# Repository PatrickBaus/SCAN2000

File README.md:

# Keithley 2000-SCAN SSR Replacement

This repository contains the KiCAD PCB project files for a [Keithley Model 2000-SCAN](https://download.tek.com/manual/2000SCAN-901-01_F-Jan-2014.pdf) replacement card. It uses solid-state relays instead of mechanical relays. See [below](#introduction) for a list of compatible devices. The design files can be found on the [releases](../../releases) page.

## Contents
- [Introduction](#introduction)
- [Design Files](#design-files)
- [Installation](#installation)
- [Accesories](#accesories)
- [Related Repositories](#related-repositories)
- [Versioning](#versioning)
- [License](#license)

## Introduction
The design is the successor of the SCAN2000 STM32 board previously released as [v1.x](https://github.com/PatrickBaus/SCAN2000/tree/v1). Instead of an STM32 microcontroller it uses an [iCE40](https://www.latticesemi.com/iCE40) FPGA to emulate the shift registers found on the 10 channel [Model 2000-SCAN](https://download.tek.com/manual/2000SCAN-901-01_F-Jan-2014.pdf) card and is also capable of decoding the protcol used by the 20-channel [Model 2000-SCAN-20](https://download.tek.com/manual/2000-20-901-01C_Jul2003_Instruction.pdf). The advantage of the FPGA is that the shift registers are implemented in hardware. The protocol spoken by the 10 channnel card requires freezing 24 bits clocked in _before_ the strobe bin is triggered, similar to the positive lookahead assertion of a [regular expression](https://en.wikipedia.org/wiki/Regular_expression). This is in stark contrast to typical protocols used by microcontrollers like, for example, [SPI](https://en.wikipedia.org/wiki/Serial_Peripheral_Interface) that uses a [chip select](https://en.wikipedia.org/wiki/Chip_select) control line to announce incoming data arriving _after_ the CS signal. A more detailed analysis of the problem can be found in the [doc/](doc/) folder.

The card was tested in a [Keithley DMM6500](https://www.tek.com/en/products/keithley/digital-multimeter/dmm6500) and a [Keithley Model 2002](https://www.tek.com/en/products/keithley/digital-multimeter/2002-series) in both configurations as a 10 channel and 20 channel card. The more recent [Keithley DMM6500](https://www.tek.com/en/products/keithley/digital-multimeter/dmm6500) supports both the older 10 channel [Model 2000-SCAN](https://download.tek.com/manual/2000SCAN-901-01_F-Jan-2014.pdf) and the newer [Model 2000-SCAN-20](https://download.tek.com/manual/2000-20-901-01C_Jul2003_Instruction.pdf) 20 channel scanner card. The same goes for the [Model 2000](https://www.tek.com/en/products/keithley/digital-multimeter/keithley-2000-series-6-digit-multimeter-scanning) and Model 2000-20. The Model 2000-20 is similar to the [Model 2000](https://www.tek.com/en/products/keithley/digital-multimeter/keithley-2000-series-6-digit-multimeter-scanning), but has a different firmware. The latest firmare of the [Model 2000](https://www.tek.com/en/products/keithley/digital-multimeter/keithley-2000-series-6-digit-multimeter-scanning) seems to support the 20 channel cards as well as suggested [here](https://www.eevblog.com/forum/circuit-studio/example-project-20-channel-solid-state-scan-card-for-k2000-dmm/msg3101128/#msg3101128). The [Model 2002](https://www.tek.com/en/products/keithley/digital-multimeter/2002-series) only supports 10 channel cards.

|DMM|Tested|Note|
|--|--|--|
|[DMM6500](https://www.tek.com/en/products/keithley/digital-multimeter/dmm6500)|:heavy_check_mark:|Works.|
|[2000](https://www.tek.com/en/products/keithley/digital-multimeter/keithley-2000-series-6-digit-multimeter-scanning)|:x:|Not tested, but should work. The latest firmware seems to support [20 channels](https://www.eevblog.com/forum/circuit-studio/example-project-20-channel-solid-state-scan-card-for-k2000-dmm/msg3101128/#msg3101128).|
|[2000-20](https://www.tek.com/en/products/keithley/digital-multimeter/keithley-2000-series-6-digit-multimeter-scanning)|:x:|Not tested, but should work.|
|[2010](https://www.tek.com/en/products/keithley/digital-multimeter/2010-series)|:heavy_check_mark:|Works, but only 10 channels cards are supported by the firmware.|
|[2001](https://www.tek.com/en/products/keithley/digital-multimeter/2001-series)|:x:|Not tested, but should work.|
|[2002](https://www.tek.com/en/products/keithley/digital-multimeter/2002-series)|:heavy_check_mark:|Works. Only 10 channels supported.|

## Design Files
The root folder contains the KiCAD files. The bill of materials can be found on the [releases](../../releases) page along with Gerber files for production.

## Installation
The source code for the FPGA and the installation instructions for the firmware can be found [here](https://github.com/PatrickBaus/SCAN2000_iCE40_Firmware). The FPGA source code must be written to the onboard SPI flash chip. One way to do so is to use an USB to SPI converter with an FT232H chip.

The SCAN2000 SSR board has two solder jumpers, ```JP1``` and ```JP2```. To enable only 10 channels close ```JP2``` and connect the two left pads of ```JP1``` together using a soldering iron. To enable 20 channel operation, leave ```JP2``` open and connect the two rightmost pads of ```JP1```.

The assembled card can then wired up and simply inserted into the multimeter. It will be supplied by the DMM through the Molex connector. To connect the scanner outputs to the, connect the screw terminals labeled ```Input``` to the DMM terminals labeled ```Input```. The same goes for the ```Sense``` terminals if operating in 4-wire mode.

## Accesories
The [Model 2000-SCAN](https://download.tek.com/manual/2000SCAN-901-01_F-Jan-2014.pdf) comes with four 10″ connectors that have a right angle 4 mm connector on one side and a tinned wire on the other. They are sold by Keithley as [CA-109A](https://download.tek.com/document/1KW-50660-1_Keithley_Test_Leads_Probes_Selector_Guide_100622.pdf) and are made by Mueller Electric. Their part numbers are [BU-0062-N-108-2 (red)](https://www.muellerelectric.com/products/bu-0062-n-108-2) and [BU-0062-N-108-0 (black)](https://www.muellerelectric.com/products/bu-0062-n-108-0). Keithley shortens the Mueller Electric parts to 10″. The same length is fine for this board as well.

## Related Repositories
See the following repositories for more information as these are part of the [design files](#design-files).

- [KiCad footprints](https://github.com/PatrickBaus/footprints.pretty)
- [KiCAD 3D models](https://github.com/PatrickBaus/footprints.3dshapes)
- [KiCAD schematic libraries](https://github.com/PatrickBaus/KiCad-libraries)

## Versioning
I use [SemVer](http://semver.org/) for versioning. For the versions available, see the [tags](../../tags) available for this repository.

- MAJOR versions in this context mean a breaking change to the external interface of the hardware like different connectors or functions.
- MINOR versions contain changes to the hardware that only affect the inner workings of the circuit, but otherwise the performance is unaffected.
- PATCH versions do not affect the schematics or invalidate older bill of materials. These changes may include updated components (to replace obsolete parts for example), an updated silkscreen, or fixed typos.

## License
This work is released under the CERN-OHL-W
See [https://ohwr.org/cern_ohl_w_v2.pdf](https://ohwr.org/cern_ohl_w_v2.pdf) or the included LICENSE file for more information.

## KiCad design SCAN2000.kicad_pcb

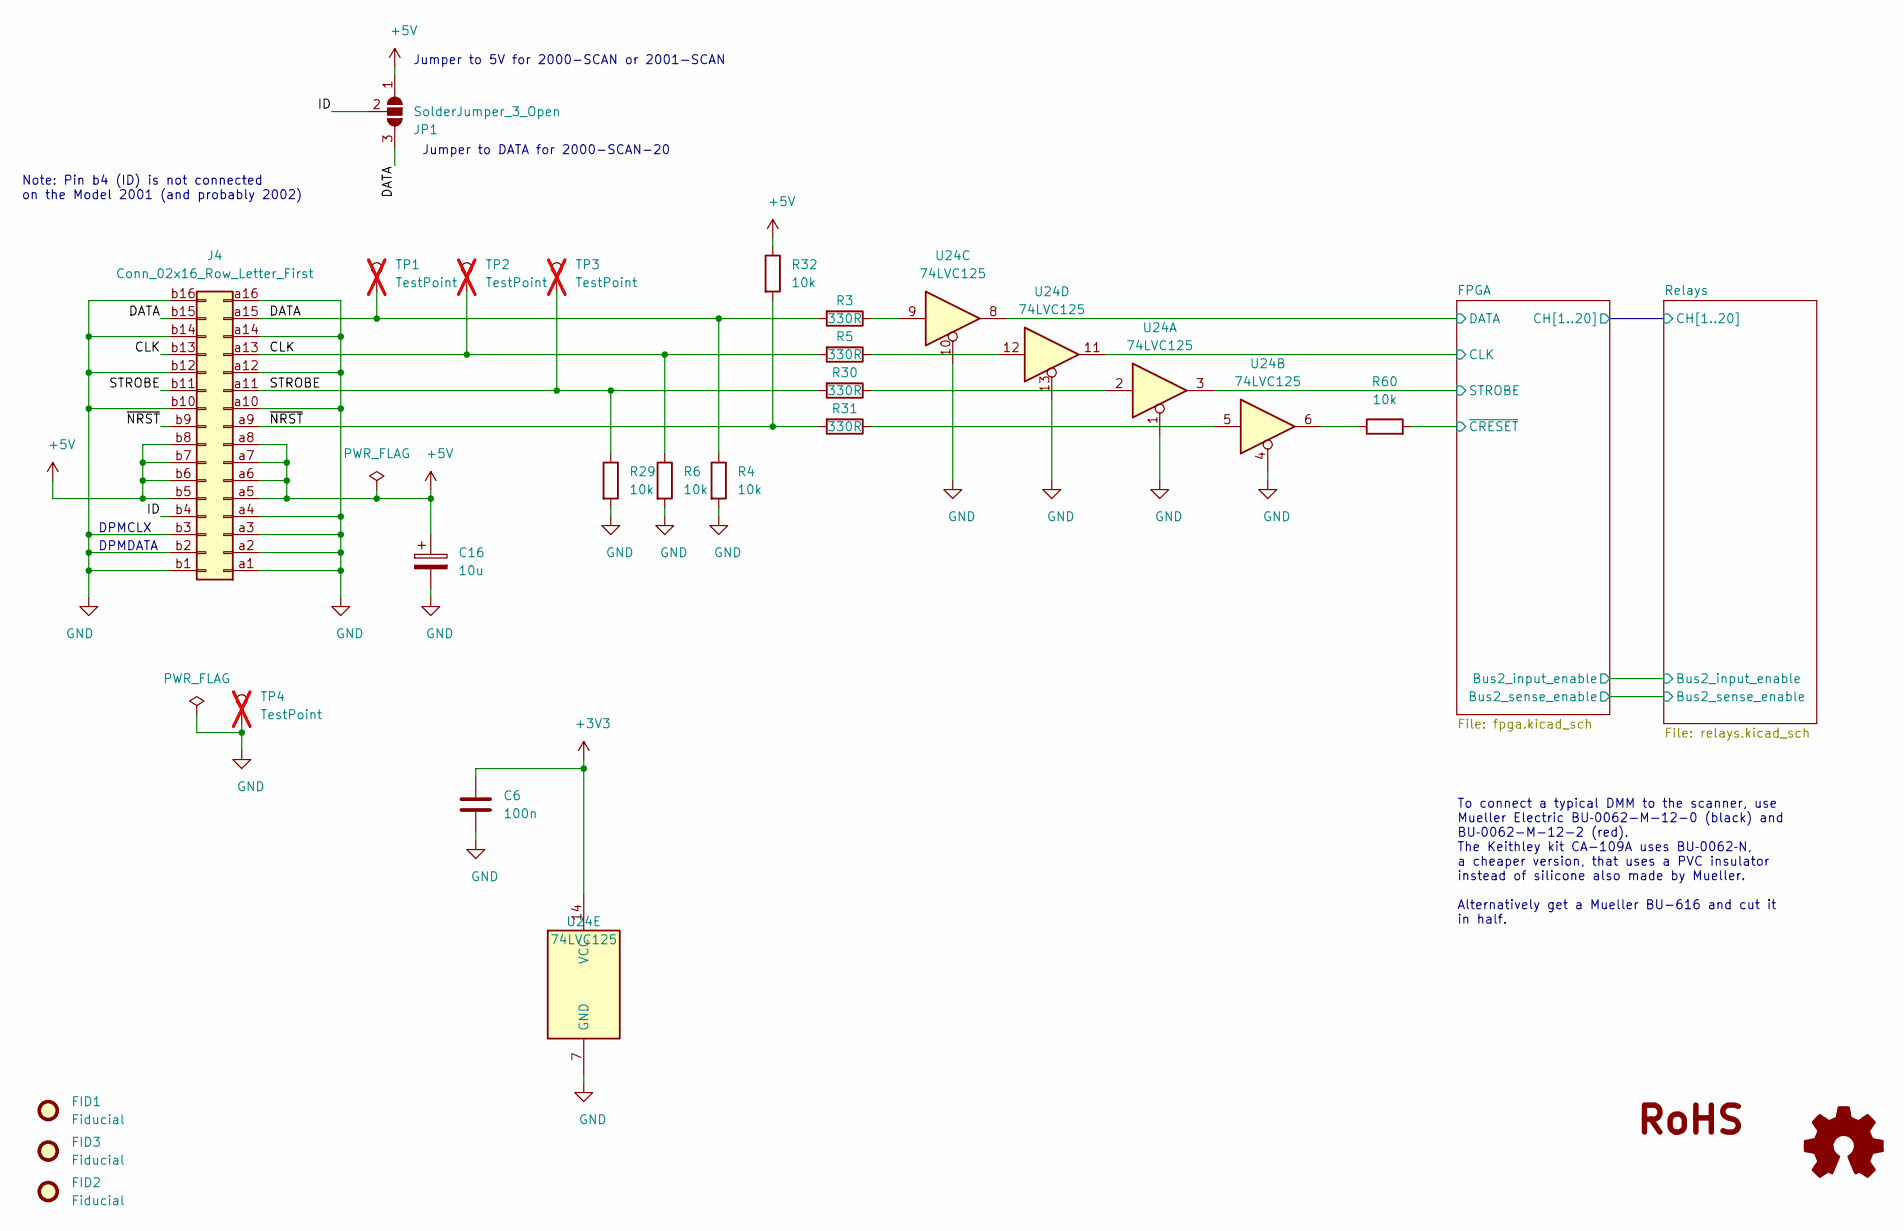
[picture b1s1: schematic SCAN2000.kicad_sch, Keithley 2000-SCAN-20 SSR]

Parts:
C6: 100n; C_0603_1608Metric
C16: 10u; CP_Radial_D6.3mm_P2.50mm
FID1, FID2, FID3: Fiducial; Fiducial_0.5mm_Mask1mm
J4: Conn_02x16_Row_Letter_First; DIN41612_B2_2x16_Male_Horizontal_THT; Digikey# 09272326804-ND
JP1: SolderJumper_3_Open; SolderJumper-3_P1.3mm_Open_Pad1.0x1.5mm
LOGO1: Logo_Open_Hardware_Small; OSHW-Logo_7.5x8mm_SilkScreen
R3, R5, R30, R31: 330R; R_0603_1608Metric
R4, R6, R29, R32, R60: 10k; R_0603_1608Metric
TP1, TP2, TP3, TP4: TestPoint; TestPoint_Loop_D2.60mm_Drill1.6mm_Beaded; not fitted
U24: 74LVC125; TSSOP-14_4.4x5mm_P0.65mm

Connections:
+3V3: C6.1, U24.14 (VCC); also elsewhere on the board
+5V: C16.1, J4.a5, J4.a6, J4.a7, J4.a8, J4.b5, J4.b6, J4.b7, J4.b8, JP1.1 (A), R32.1; also elsewhere on the board
/CLK: J4.a13, J4.b13, R5.2, R6.1, TP2.1
/DATA: J4.a15, J4.b15, JP1.3 (B), R3.2, R4.1, TP1.1
/FPGA/CLK: U24.11; also elsewhere on the board
/FPGA/DATA: U24.8; also elsewhere on the board
/FPGA/STROBE: U24.3; also elsewhere on the board
/FPGA/~CRESET: R60.2; also elsewhere on the board
/ID: J4.b4, JP1.2 (C)
/STROBE: J4.a11, J4.b11, R29.1, R30.2, TP3.1
/~NRST: J4.a9, J4.b9, R31.2, R32.2
GND: C6.2, C16.2, J4.a1, J4.a2, J4.a3, J4.a4, J4.a10, J4.a12, J4.a14, J4.a16, J4.b1, J4.b2, J4.b3, J4.b10, J4.b12, J4.b14, J4.b16, R4.2, R6.2, R29.2, TP4.1, U24.1, U24.4, U24.7 (GND), U24.10, U24.13; also elsewhere on the board
unnamed: R3.1, U24.9
unnamed: R5.1, U24.12
unnamed: R30.1, U24.2
unnamed: R31.1, U24.5
unnamed: R60.1, U24.6

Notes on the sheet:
DPMDATA
DPMCLX
Jumper to 5V for 2000-SCAN or 2001-SCAN
Jumper to DATA for 2000-SCAN-20
To connect a typical DMM to the scanner, use Mueller Electric BU‐0062-M-12-0 (black) and BU‐0062-M-12-2 (red). The Keithley kit CA-109A uses BU‐0062‐N, a cheaper version, that uses a PVC insulator instead of silicone also made by Mueller. Alternatively get a Mueller BU-616 and cut it in half.
Note: Pin b4 (ID) is not connected on the Model 2001 (and probably 2002)

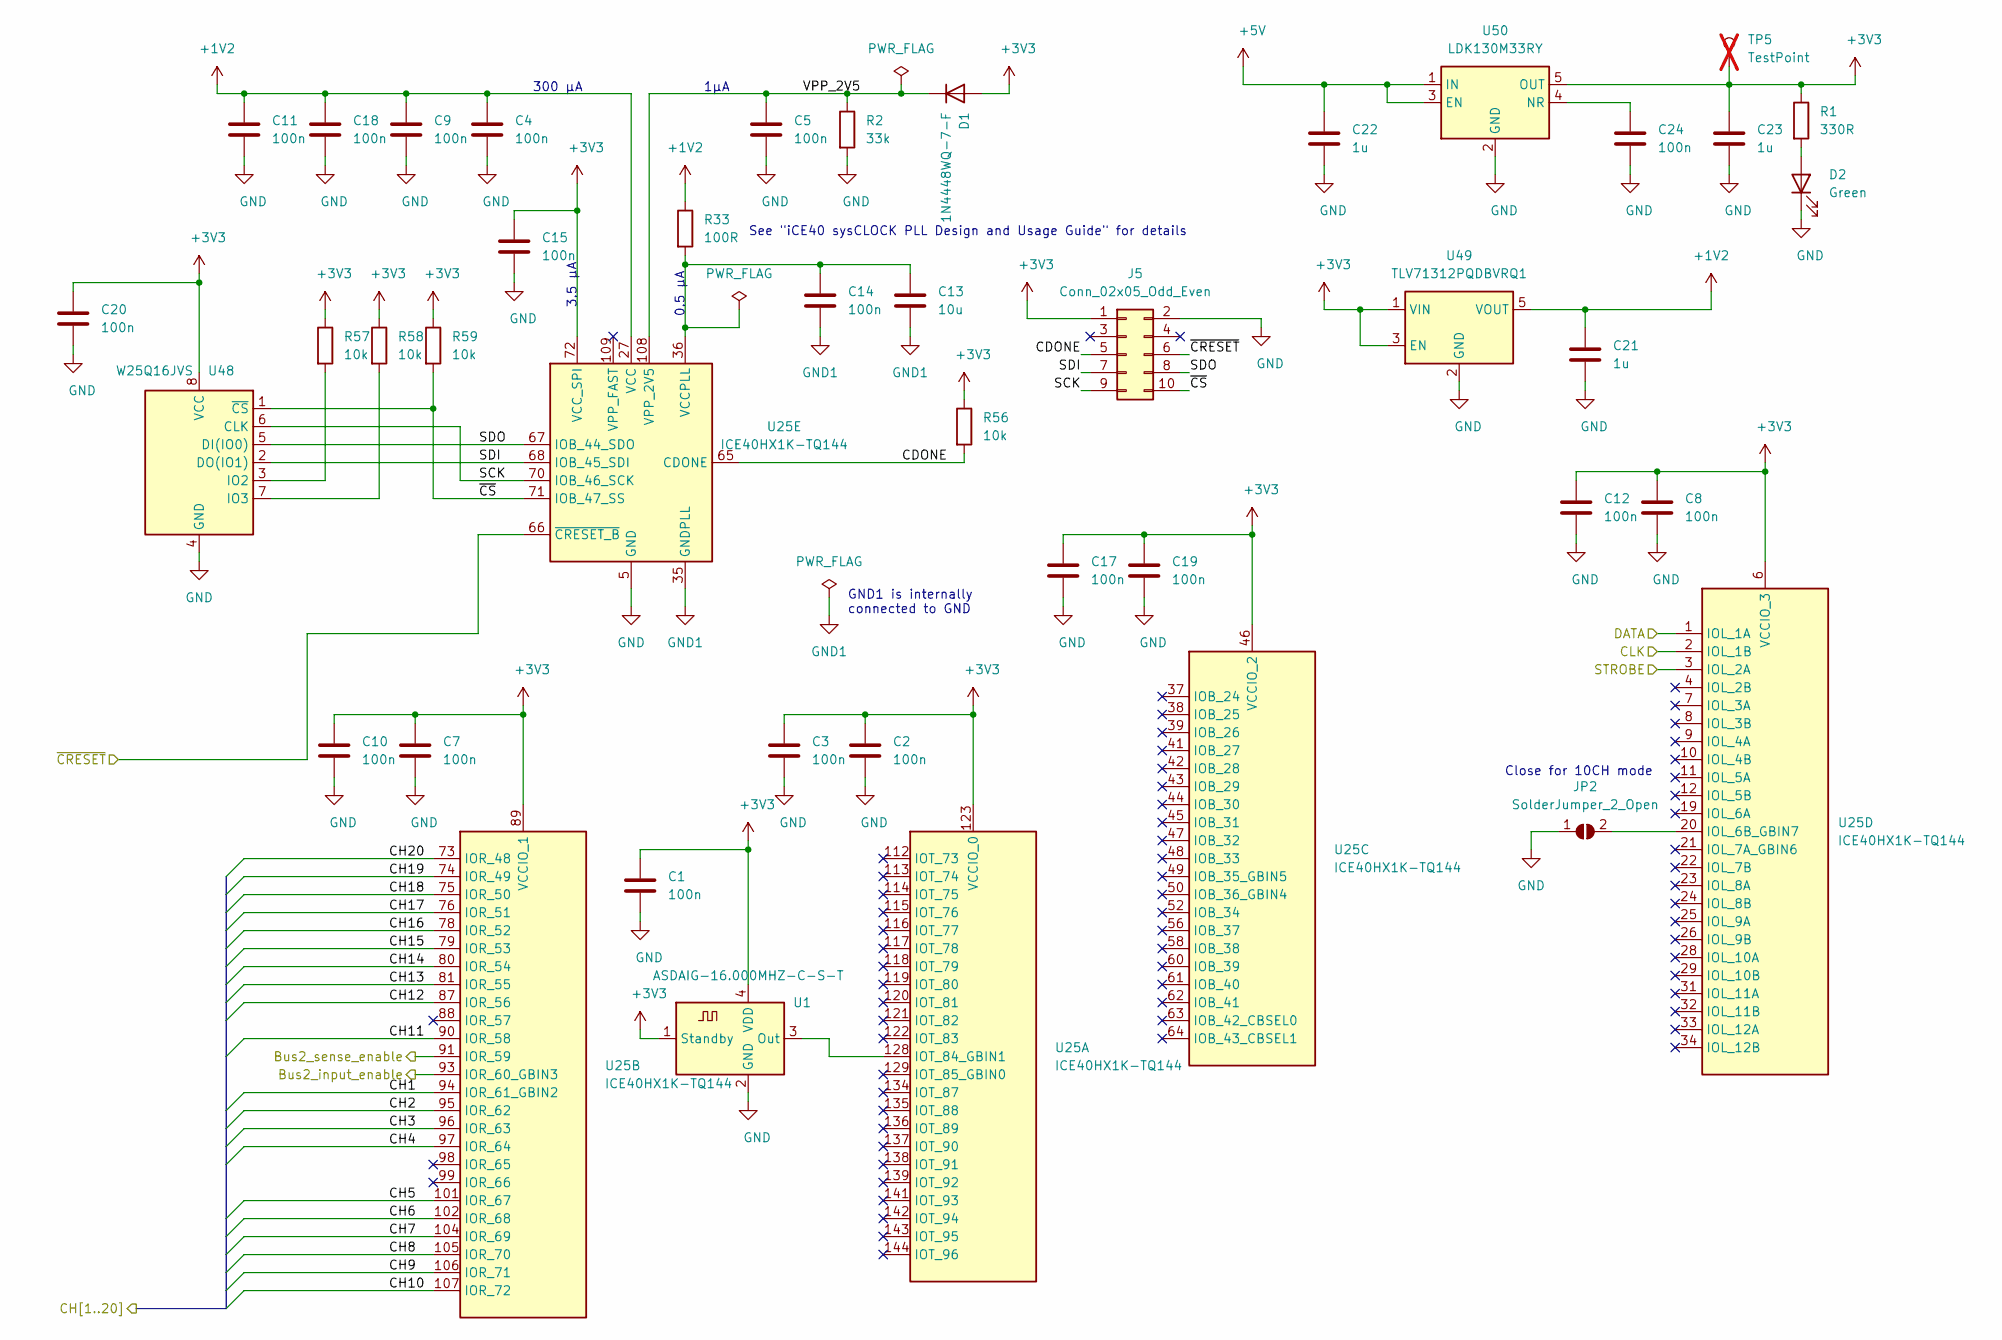
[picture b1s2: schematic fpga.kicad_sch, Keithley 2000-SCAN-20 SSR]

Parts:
C1, C2, C3, C4, C5, C7, C8, C9, C10, C11, C12, C14, C15, C17, C18, C19, C20, C24: 100n; C_0603_1608Metric
C13: 10u; C_0805_2012Metric
C21, C22, C23: 1u; C_0805_2012Metric
D1: 1N4448WQ-7-F; D_SOD-123
D2: Green; LED_0603_1608Metric
J5: Conn_02x05_Odd_Even; IDC-Header_2x05_P2.54mm_Vertical
JP2: SolderJumper_2_Open; SolderJumper-2_P1.3mm_Open_Pad1.0x1.5mm
R1: 330R; R_0603_1608Metric
R2: 33k; R_0603_1608Metric
R33: 100R; R_0603_1608Metric
R56, R57, R58, R59: 10k; R_0603_1608Metric
TP5: TestPoint; TestPoint_Loop_D2.60mm_Drill1.6mm_Beaded; not fitted
U1: ASDAIG-16.000MHZ-C-S-T; Oscillator_SMD_Abracon_ASDMB-4Pin_2.5x2.0mm
U25: ICE40HX1K-TQ144; TQFP-144_20x20mm_P0.5mm
U48: W25Q16JVS; SOIC-8_3.9x4.9mm_P1.27mm
U49: TLV71312PQDBVRQ1; SOT-23-5
U50: LDK130M33RY; SOT-23-5

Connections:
+1V2: C4.1, C9.1, C11.1, C18.1, C21.1, R33.1, U25.27 (VCC), U25.51 (VCC), U25.92 (VCC), U25.111 (VCC), U49.5 (VOUT)
+3V3: C1.1, C2.1, C3.1, C7.1, C8.1, C10.1, C12.1, C15.1, C17.1, C19.1, C20.1, C23.1, D1.2 (A), J5.1, R1.1, R56.1, R57.1, R58.1, R59.1, TP5.1, U1.1 (Standby), U1.4 (VDD), U25.6 (VCCIO_3), U25.30 (VCCIO_3), U25.46 (VCCIO_2), U25.57 (VCCIO_2), U25.72 (VCC_SPI), U25.89 (VCCIO_1), U25.100 (VCCIO_1), U25.123 (VCCIO_0), U25.133 (VCCIO_0), U48.8 (VCC), U49.1 (VIN), U49.3 (EN), U50.5 (OUT); also elsewhere on the board
+5V: C22.1, U50.1 (IN), U50.3 (EN); also elsewhere on the board
/FPGA/Bus2_input_enable: U25.93 (IOR_60_GBIN3); also elsewhere on the board
/FPGA/Bus2_sense_enable: U25.91 (IOR_59); also elsewhere on the board
/FPGA/CDONE: J5.5, R56.2, U25.65 (CDONE)
/FPGA/CH1: U25.94 (IOR_61_GBIN2); also elsewhere on the board
/FPGA/CH2: U25.95 (IOR_62); also elsewhere on the board
/FPGA/CH3: U25.96 (IOR_63); also elsewhere on the board
/FPGA/CH4: U25.97 (IOR_64); also elsewhere on the board
/FPGA/CH5: U25.101 (IOR_67); also elsewhere on the board
/FPGA/CH6: U25.102 (IOR_68); also elsewhere on the board
/FPGA/CH7: U25.104 (IOR_69); also elsewhere on the board
/FPGA/CH8: U25.105 (IOR_70); also elsewhere on the board
/FPGA/CH9: U25.106 (IOR_71); also elsewhere on the board
/FPGA/CH10: U25.107 (IOR_72); also elsewhere on the board
/FPGA/CH11: U25.90 (IOR_58); also elsewhere on the board
/FPGA/CH12: U25.87 (IOR_56); also elsewhere on the board
/FPGA/CH13: U25.81 (IOR_55); also elsewhere on the board
/FPGA/CH14: U25.80 (IOR_54); also elsewhere on the board
/FPGA/CH15: U25.79 (IOR_53); also elsewhere on the board
/FPGA/CH16: U25.78 (IOR_52); also elsewhere on the board
/FPGA/CH17: U25.76 (IOR_51); also elsewhere on the board
/FPGA/CH18: U25.75 (IOR_50); also elsewhere on the board
/FPGA/CH19: U25.74 (IOR_49); also elsewhere on the board
/FPGA/CH20: U25.73 (IOR_48); also elsewhere on the board
/FPGA/CLK: U25.2 (IOL_1B); also elsewhere on the board
/FPGA/DATA: U25.1 (IOL_1A); also elsewhere on the board
/FPGA/SCK: J5.9, U25.70 (IOB_46_SCK), U48.6 (CLK)
/FPGA/SDI: J5.7, U25.68 (IOB_45_SDI), U48.2 (DO(IO1))
/FPGA/SDO: J5.8, U25.67 (IOB_44_SDO), U48.5 (DI(IO0))
/FPGA/STROBE: U25.3 (IOL_2A); also elsewhere on the board
/FPGA/VPP_2V5: C5.1, D1.1 (K), R2.1, U25.108 (VPP_2V5)
/FPGA/~CRESET: J5.6, U25.66 (~CRESET_B); also elsewhere on the board
/FPGA/~CS: J5.10, R59.2, U25.71 (IOB_47_SS), U48.1 (~CS)
GND: C1.2, C2.2, C3.2, C4.2, C5.2, C7.2, C8.2, C9.2, C10.2, C11.2, C12.2, C15.2, C17.2, C18.2, C19.2, C20.2, C21.2, C22.2, C23.2, C24.2, D2.1 (K), J5.2, JP2.1 (A), R2.2, U1.2 (GND), U25.5 (GND), U25.13 (GND), U25.14 (GND), U25.59 (GND), U25.69 (GND), U25.86 (GND), U25.103 (GND), U25.132 (GND), U25.140 (GND), U48.4 (GND), U49.2 (GND), U50.2 (GND); also elsewhere on the board
GND1: C13.2, C14.2, U25.35 (GNDPLL)
unnamed: D2.2 (A), R1.2
unnamed: JP2.2 (B), U25.20 (IOL_6B_GBIN7)
unnamed: U1.3 (Out), U25.128 (IOT_84_GBIN1)
unnamed: C13.1, C14.1, R33.2, U25.36 (VCCPLL)
unnamed: R57.2, U48.3 (IO2)
unnamed: R58.2, U48.7 (IO3)
unnamed: C24.1, U50.4 (NR)

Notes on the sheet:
1µA
Close for 10CH mode
3.5 µA
See "iCE40 sysCLOCK PLL Design and Usage Guide" for details
300 µA
0.5 µA
GND1 is internally connected to GND

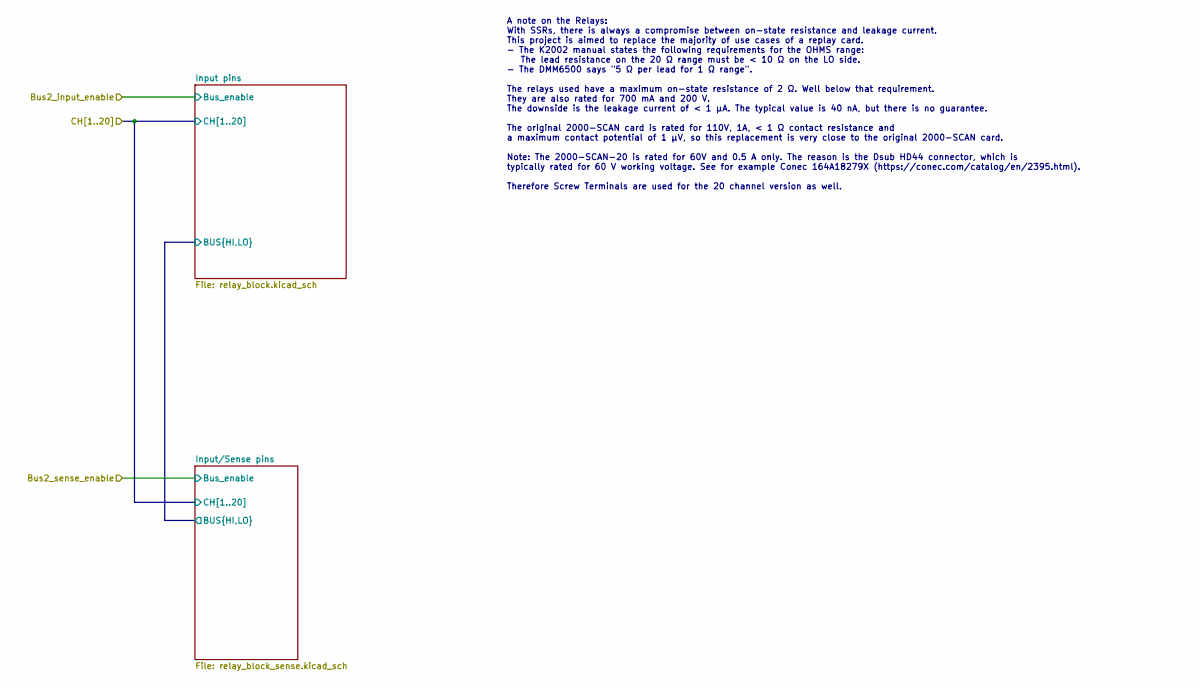
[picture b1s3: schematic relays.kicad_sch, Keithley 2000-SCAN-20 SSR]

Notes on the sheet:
A note on the Relays: With SSRs, there is always a compromise between on-state resistance and leakage current. This project is aimed to replace the majority of use cases of a replay card. - The K2002 manual states the following requirements for the OHMS range: The lead resistance on the 20 Ω range 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

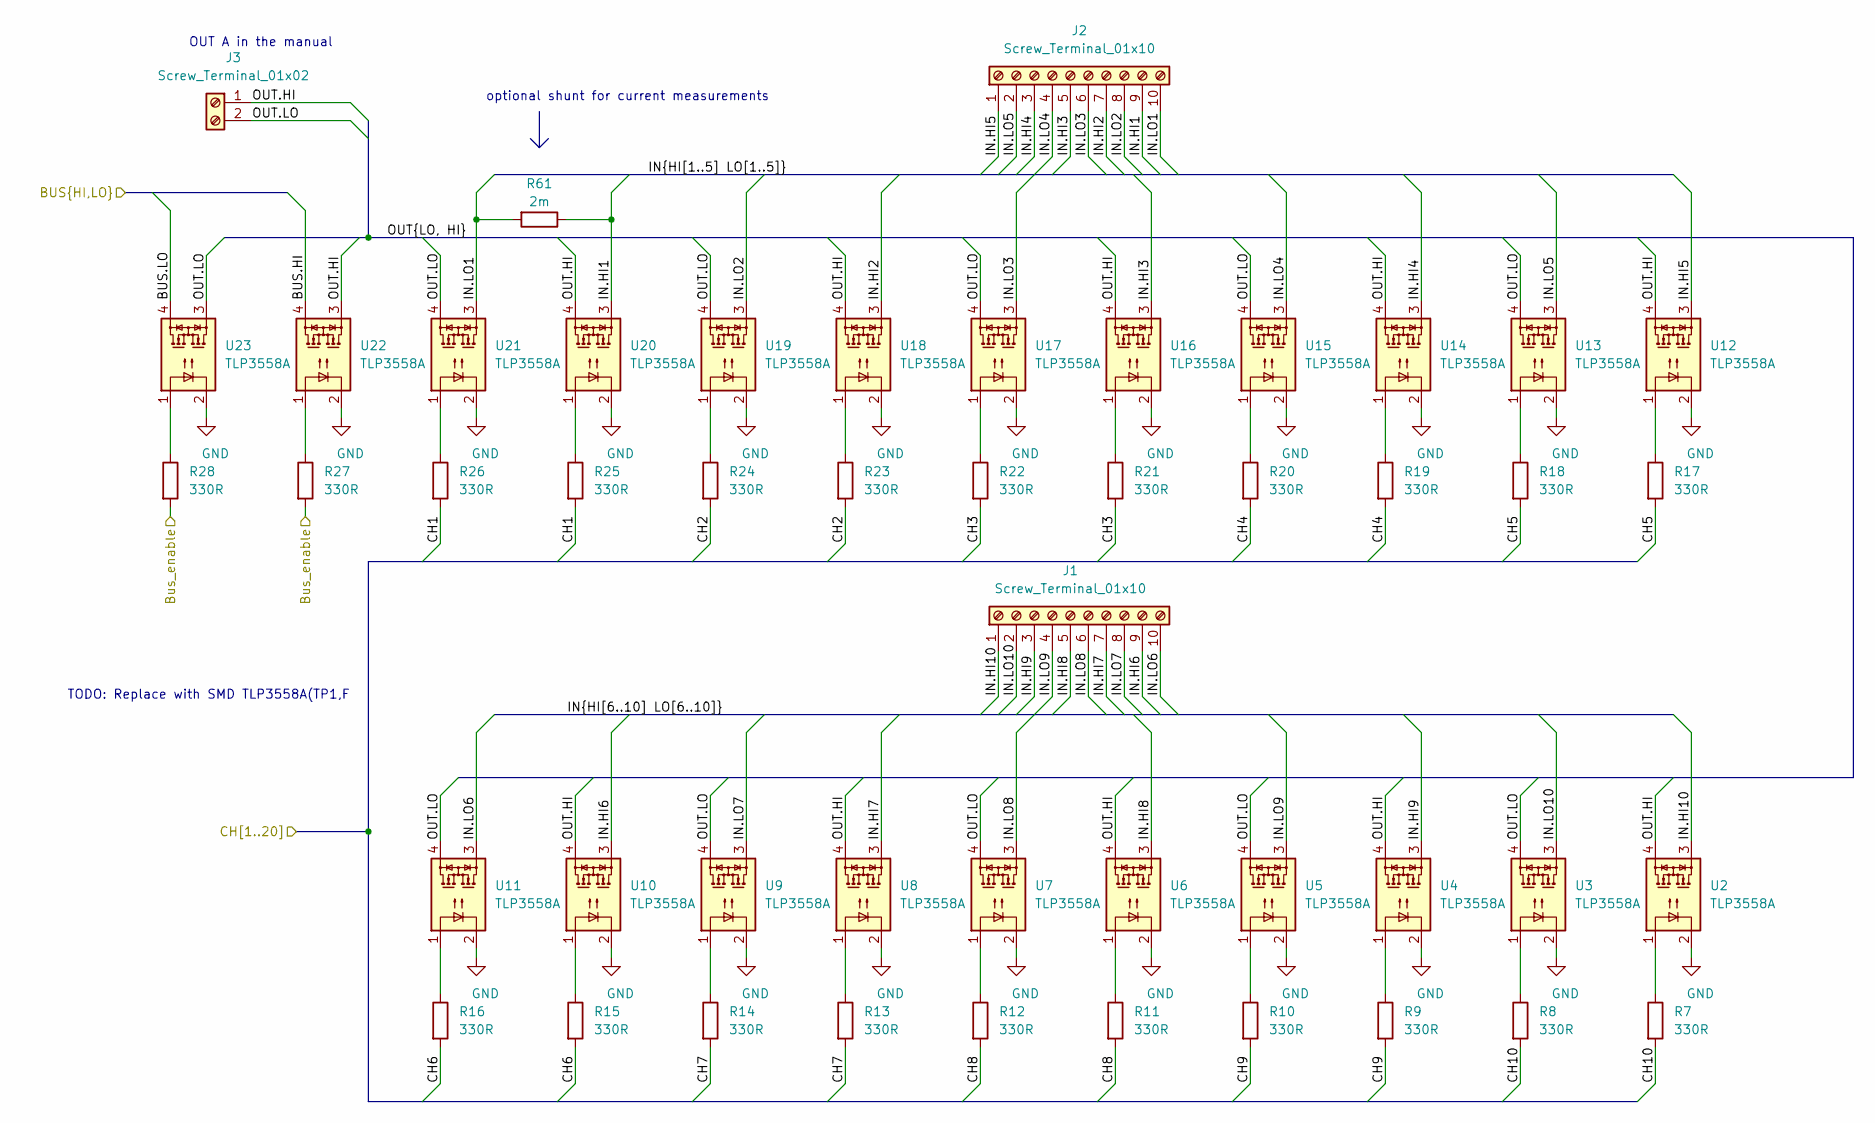
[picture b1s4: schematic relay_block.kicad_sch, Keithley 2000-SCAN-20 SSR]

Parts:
J1, J2: Screw_Terminal_01x10; TerminalBlock_Phoenix_SMKDSN-1,5-10-5.08_1x10_P5.08mm_Horiz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
J3: Screw_Terminal_01x02; TerminalBlock_Phoenix_SMKDSN-1,5-2-5.08_1x02_P5.08mm_Horizo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
R7, R8, R9, R10, R11, R12, R13, R14, R15, R16, R17, R18, R19, R20, R21, R22, R23, R24, R25, R26, R27, R28: 330R; R_0603_1608Metric
R61: 2m; R_2512_6332Metric
U2, U3, U4, U5, U6, U7, U8, U9, U10, U11, U12, U13, U14, U15, U16, U17, U18, U19, U20, U21, U22, U23: TLP3558A; DIP-4_W7.62mm

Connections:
/FPGA/Bus2_input_enable: R27.2, R28.2; also elsewhere on the board
/FPGA/CH1: R25.2, R26.2; also elsewhere on the board
/FPGA/CH2: R23.2, R24.2; also elsewhere on the board
/FPGA/CH3: R21.2, R22.2; also elsewhere on the board
/FPGA/CH4: R19.2, R20.2; also elsewhere on the board
/FPGA/CH5: R17.2, R18.2; also elsewhere on the board
/FPGA/CH6: R15.2, R16.2; also elsewhere on the board
/FPGA/CH7: R13.2, R14.2; also elsewhere on the board
/FPGA/CH8: R11.2, R12.2; also elsewhere on the board
/FPGA/CH9: R9.2, R10.2; also elsewhere on the board
/FPGA/CH10: R7.2, R8.2; also elsewhere on the board
/Relays/Input pins/BUS.HI: U22.4; also elsewhere on the board
/Relays/Input pins/BUS.LO: U23.4; also elsewhere on the board
/Relays/Input pins/IN.HI1: J2.9, R61.1, U20.3
/Relays/Input pins/IN.HI2: J2.7, U18.3
/Relays/Input pins/IN.HI3: J2.5, U16.3
/Relays/Input pins/IN.HI4: J2.3, U14.3
/Relays/Input pins/IN.HI5: J2.1, U12.3
/Relays/Input pins/IN.HI6: J1.9, U10.3
/Relays/Input pins/IN.HI7: J1.7, U8.3
/Relays/Input pins/IN.HI8: J1.5, U6.3
/Relays/Input pins/IN.HI9: J1.3, U4.3
/Relays/Input pins/IN.HI10: J1.1, U2.3
/Relays/Input pins/IN.LO1: J2.10, R61.2, U21.3
/Relays/Input pins/IN.LO2: J2.8, U19.3
/Relays/Input pins/IN.LO3: J2.6, U17.3
/Relays/Input pins/IN.LO4: J2.4, U15.3
/Relays/Input pins/IN.LO5: J2.2, U13.3
/Relays/Input pins/IN.LO6: J1.10, U11.3
/Relays/Input pins/IN.LO7: J1.8, U9.3
/Relays/Input pins/IN.LO8: J1.6, U7.3
/Relays/Input pins/IN.LO9: J1.4, U5.3
/Relays/Input pins/IN.LO10: J1.2, U3.3
/Relays/Input pins/OUT.HI: J3.1, U2.4, U4.4, U6.4, U8.4, U10.4, U12.4, U14.4, U16.4, U18.4, U20.4, U22.3
/Relays/Input pins/OUT.LO: J3.2, U3.4, U5.4, U7.4, U9.4, U11.4, U13.4, U15.4, U17.4, U19.4, U21.4, U23.3
GND: U2.2, U3.2, U4.2, U5.2, U6.2, U7.2, U8.2, U9.2, U10.2, U11.2, U12.2, U13.2, U14.2, U15.2, U16.2, U17.2, U18.2, U19.2, U20.2, U21.2, U22.2, U23.2; also elsewhere on the board
unnamed: R7.1, U2.1
unnamed: R8.1, U3.1
unnamed: R9.1, U4.1
unnamed: R10.1, U5.1
unnamed: R11.1, U6.1
unnamed: R12.1, U7.1
unnamed: R13.1, U8.1
unnamed: R14.1, U9.1
unnamed: R15.1, U10.1
unnamed: R16.1, U11.1
unnamed: R17.1, U12.1
unnamed: R18.1, U13.1
unnamed: R19.1, U14.1
unnamed: R20.1, U15.1
unnamed: R21.1, U16.1
unnamed: R22.1, U17.1
unnamed: R23.1, U18.1
unnamed: R24.1, U19.1
unnamed: R25.1, U20.1
unnamed: R26.1, U21.1
unnamed: R27.1, U22.1
unnamed: R28.1, U23.1

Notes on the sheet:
optional shunt for current measurements
TODO: Replace with SMD TLP3558A(TP1,F
OUT A in the manual

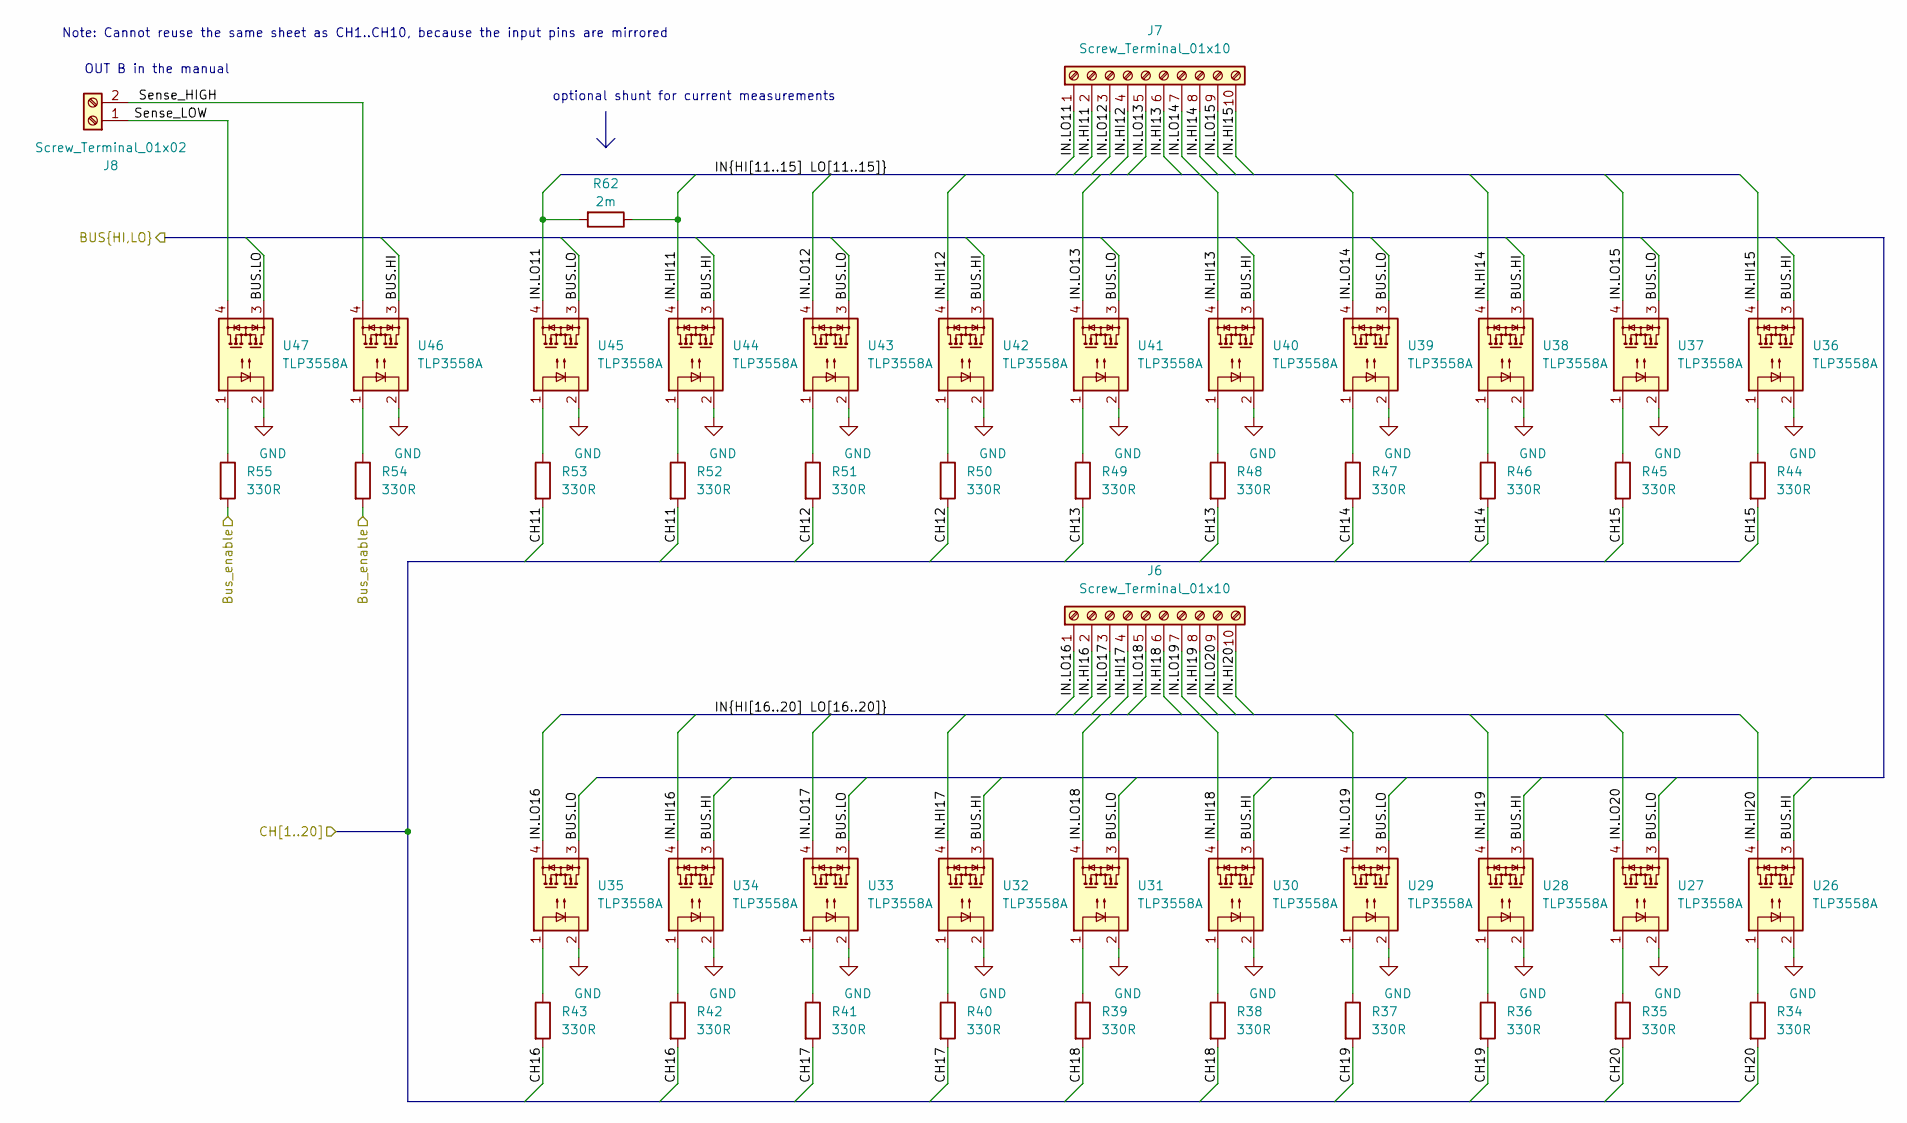
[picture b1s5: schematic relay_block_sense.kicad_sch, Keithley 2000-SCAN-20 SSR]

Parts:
J6, J7: Screw_Terminal_01x10; TerminalBlock_Phoenix_SMKDSN-1,5-10-5.08_1x10_P5.08mm_Horiz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
J8: Screw_Terminal_01x02; TerminalBlock_Phoenix_SMKDSN-1,5-2-5.08_1x02_P5.08mm_Horizo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
R34, R35, R36, R37, R38, R39, R40, R41, R42, R43, R44, R45, R46, R47, R48, R49, R50, R51, R52, R53, R54, R55: 330R; R_0603_1608Metric
R62: 2m; R_2512_6332Metric
U26, U27, U28, U29, U30, U31, U32, U33, U34, U35, U36, U37, U38, U39, U40, U41, U42, U43, U44, U45, U46, U47: TLP3558A; DIP-4_W7.62mm

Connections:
/FPGA/Bus2_sense_enable: R54.2, R55.2; also elsewhere on the board
/FPGA/CH11: R52.2, R53.2; also elsewhere on the board
/FPGA/CH12: R50.2, R51.2; also elsewhere on the board
/FPGA/CH13: R48.2, R49.2; also elsewhere on the board
/FPGA/CH14: R46.2, R47.2; also elsewhere on the board
/FPGA/CH15: R44.2, R45.2; also elsewhere on the board
/FPGA/CH16: R42.2, R43.2; also elsewhere on the board
/FPGA/CH17: R40.2, R41.2; also elsewhere on the board
/FPGA/CH18: R38.2, R39.2; also elsewhere on the board
/FPGA/CH19: R36.2, R37.2; also elsewhere on the board
/FPGA/CH20: R34.2, R35.2; also elsewhere on the board
/Relays/Input pins/BUS.HI: U26.3, U28.3, U30.3, U32.3, U34.3, U36.3, U38.3, U40.3, U42.3, U44.3, U46.3; also elsewhere on the board
/Relays/Input pins/BUS.LO: U27.3, U29.3, U31.3, U33.3, U35.3, U37.3, U39.3, U41.3, U43.3, U45.3, U47.3; also elsewhere on the board
/Relays/Input/Sense pins/IN.HI11: J7.2, R62.1, U44.4
/Relays/Input/Sense pins/IN.HI12: J7.4, U42.4
/Relays/Input/Sense pins/IN.HI13: J7.6, U40.4
/Relays/Input/Sense pins/IN.HI14: J7.8, U38.4
/Relays/Input/Sense pins/IN.HI15: J7.10, U36.4
/Relays/Input/Sense pins/IN.HI16: J6.2, U34.4
/Relays/Input/Sense pins/IN.HI17: J6.4, U32.4
/Relays/Input/Sense pins/IN.HI18: J6.6, U30.4
/Relays/Input/Sense pins/IN.HI19: J6.8, U28.4
/Relays/Input/Sense pins/IN.HI20: J6.10, U26.4
/Relays/Input/Sense pins/IN.LO11: J7.1, R62.2, U45.4
/Relays/Input/Sense pins/IN.LO12: J7.3, U43.4
/Relays/Input/Sense pins/IN.LO13: J7.5, U41.4
/Relays/Input/Sense pins/IN.LO14: J7.7, U39.4
/Relays/Input/Sense pins/IN.LO15: J7.9, U37.4
/Relays/Input/Sense pins/IN.LO16: J6.1, U35.4
/Relays/Input/Sense pins/IN.LO17: J6.3, U33.4
/Relays/Input/Sense pins/IN.LO18: J6.5, U31.4
/Relays/Input/Sense pins/IN.LO19: J6.7, U29.4
/Relays/Input/Sense pins/IN.LO20: J6.9, U27.4
/Relays/Input/Sense pins/Sense_HIGH: J8.2, U46.4
/Relays/Input/Sense pins/Sense_LOW: J8.1, U47.4
GND: U26.2, U27.2, U28.2, U29.2, U30.2, U31.2, U32.2, U33.2, U34.2, U35.2, U36.2, U37.2, U38.2, U39.2, U40.2, U41.2, U42.2, U43.2, U44.2, U45.2, U46.2, U47.2; also elsewhere on the board
unnamed: R34.1, U26.1
unnamed: R35.1, U27.1
unnamed: R36.1, U28.1
unnamed: R37.1, U29.1
unnamed: R38.1, U30.1
unnamed: R39.1, U31.1
unnamed: R40.1, U32.1
unnamed: R41.1, U33.1
unnamed: R42.1, U34.1
unnamed: R43.1, U35.1
unnamed: R44.1, U36.1
unnamed: R45.1, U37.1
unnamed: R46.1, U38.1
unnamed: R47.1, U39.1
unnamed: R48.1, U40.1
unnamed: R49.1, U41.1
unnamed: R50.1, U42.1
unnamed: R51.1, U43.1
unnamed: R52.1, U44.1
unnamed: R53.1, U45.1
unnamed: R54.1, U46.1
unnamed: R55.1, U47.1

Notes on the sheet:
Note: Cannot reuse the same sheet as CH1..CH10, because the input pins are mirrored
optional shunt for current measurements
OUT B in the manual

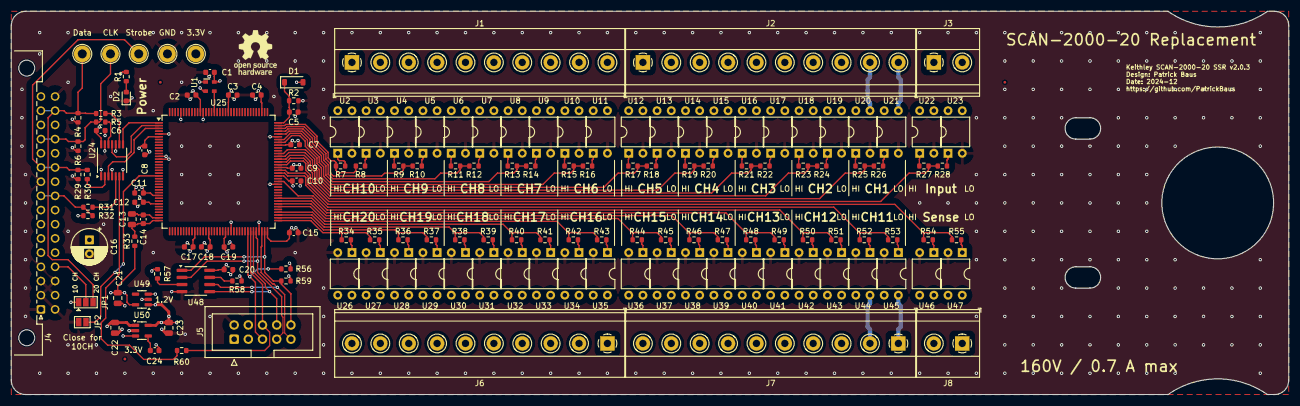
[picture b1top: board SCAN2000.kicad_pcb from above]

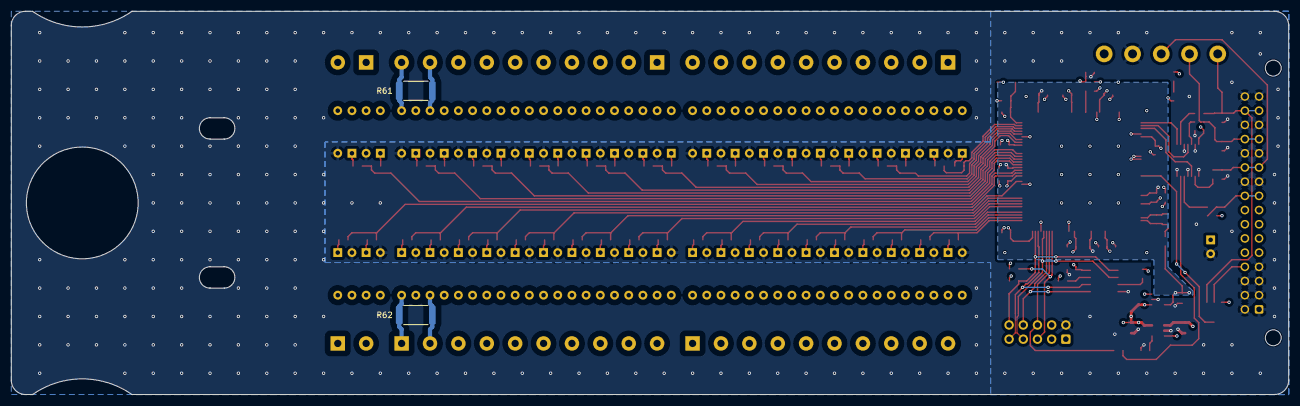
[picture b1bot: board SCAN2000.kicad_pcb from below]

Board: 4 copper layers, 228.6 x 68.6 mm, 157 parts (2 on the bottom side), 144 nets.

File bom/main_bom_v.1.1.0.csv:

Component,Description,Part,References,Value,Footprint,Quantity Per PCB,Datasheet,MFN,PN,DNP,Alternative
1,Unpolarized capacitor,C,C3 C6 C8,100n,C_0603_1608Metric,3,~,Kemet,C0603C104K5RACAUTO,,
2,Polarized capacitor,C_Polarized,C1,10u,CP_Radial_D6.3mm_P2.50mm,1,~,Nichicon,ULD2A100MED1TD,,
3,Unpolarized capacitor,C,C2 C5,1u,C_0805_2012Metric,2,~,TDK,CGA4J3X7R1H105M125AB,,
4,Unpolarized capacitor,C,C7,4.7u,C_1206_3216Metric,1,~,TDK,CGA5L3X7R1H475M160AE,,
5,Light emitting diode,LED,D1 D2,Green,LED_0603_1608Metric,2,~,Kingbright,APT1608SGC,,
6,"Generic connector, single row, 01x02, script generated (kicad-library-utils/schlib/autogen/connector/)",Conn_01x02,J3,Conn_01x02,PinHeader_1x02_P2.54mm_Vertical,1,~,Amphenol FCI,54102-T0800LF,,
7,"Generic connector, single row, 01x05, script generated (kicad-library-utils/schlib/autogen/connector/)",Conn_01x05,J2,Conn_01x05,PinHeader_1x05_P2.54mm_Vertical,1,~,Amphenol FCI,10129380-905001BLF,,
8,"Generic connector, double row, 02x16, row letter first pin numbering scheme (pin number consists of a letter for the row and a number for the pin index in this row. a1, ..., aN; b1, ..., bN), script generated (kicad-library-utils/schlib/autogen/connector/)",Conn_02x16_Row_Letter_First,J1,Conn_02x16_Row_Letter_First,DIN41612_B2_2x16_Male_Horizontal_THT,1,~,Molex,85050-0000,,
9,"Generic screw terminal, single row, 01x02, script generated (kicad-library-utils/schlib/autogen/connector/)",Screw_Terminal_01x02,J4 J7,Screw_Terminal_01x02,"TerminalBlock_Phoenix_SMKDSN-1,5-2-5.08_1x02_P5.08mm_Horizontal",2,~,Phoenix Contact,1869211,,
10,"Generic screw terminal, single row, 01x10, script generated (kicad-library-utils/schlib/autogen/connector/)",Screw_Terminal_01x10,J5 J6 J8 J9,Screw_Terminal_01x10,"TerminalBlock_Phoenix_SMKDSN-1,5-10-5.08_1x10_P5.08mm_Horizontal",4,~,Phoenix Contact,1869295,,
11,Resistor,R,R2 R3 R4 R9,10k,R_0603_1608Metric,4,~,Vishay,CRCW060310K0JNEB,,
12,Resistor,R,R16 R17 R40 R41,2m,R_2512_6332Metric,4,~,TT Electronics,ULRB1-2512-R002-F-LF-SLT,1,
13,Resistor,R,R1 R5 R6 R7 R8 R10 R11 R12 R13 R14 R15 R18 R19 R20 R21 R22 R23 R24 R25 R26 R27 R28 R29 R30 R31 R32 R33 R34 R35 R36 R37 R38 R39 R42 R43 R44 R45 R46 R47 R48 R49 R50 R51 R52 R53 R54 R55 R56 R57 R58 R59,330R,R_0603_1608Metric,51,~,Vishay,CRCW0603330RJNEB,,
14,"ARM Cortex-M0+ MCU, 128KB flash, 36KB RAM, 64MHz, 2.0-3.6V, 29 GPIO, LQFP-32",STM32G070xB,U3,STM32G070KBT6,LQFP-32_7x7mm_P0.8mm,1,https://www.st.com/resource/en/datasheet/stm32g070kb.pdf,ST Microelectronics,STM32G070KBT6,,
15,"MOSFET Photorelay 1-Form-A, Voff 60V, Ion 0,5A, DIP4",TLP222A,U4 U5 U6 U7 U8 U9 U10 U11 U12 U13 U14 U15 U16 U17 U18 U19 U20 U21 U22 U23 U24 U25 U26 U27 U28 U29 U30 U31 U32 U33 U34 U35 U36 U37 U38 U39 U40 U41 U42 U43 U44 U45 U46 U47,TLP3558A,DIP-4_W7.62mm,44,https://toshiba.semicon-storage.com/info/docget.jsp?did=6032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,Toshiba,TLP3558A(F,,
16,"Low Noise, High PSRR, 200mA Low Drop 1.8V Regulator, SOT-23-5",TPS73018DBV,U1,TPS73233DBVR,SOT-23-5,1,https://www.ti.com/lit/ds/symlink/tps732.pdf,Texas Instruments,TPS73233DBVR,,TPS73233DBVT





Component Groups:,16
Component Count:,123
Fitted Components:,123
Number of PCBs:,1
Total components:,123
Schematic Version:,v.1.1.0
Schematic Date:,2022-01-11
PCB Variant:,['default']
BoM Date:,2022-01-18T00:36:55 CET
Schematic Source:,/home/maat/Documents/Uni/Physik/Phd/SCAN2000STM32/KiCAD/main.kicad_sch
KiCad Version:,Eeschema 6.0.0

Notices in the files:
SCAN2000.kicad_pcb:
Copyright (©) 2024, Patrick Baus
Licensed under CERN-OHL-W
main.kicad_pcb:
Licensed under CERN OHL v.1.2
